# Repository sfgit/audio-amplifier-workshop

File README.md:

# audio-amplifier-workshop
simple audio amplifier workshop files

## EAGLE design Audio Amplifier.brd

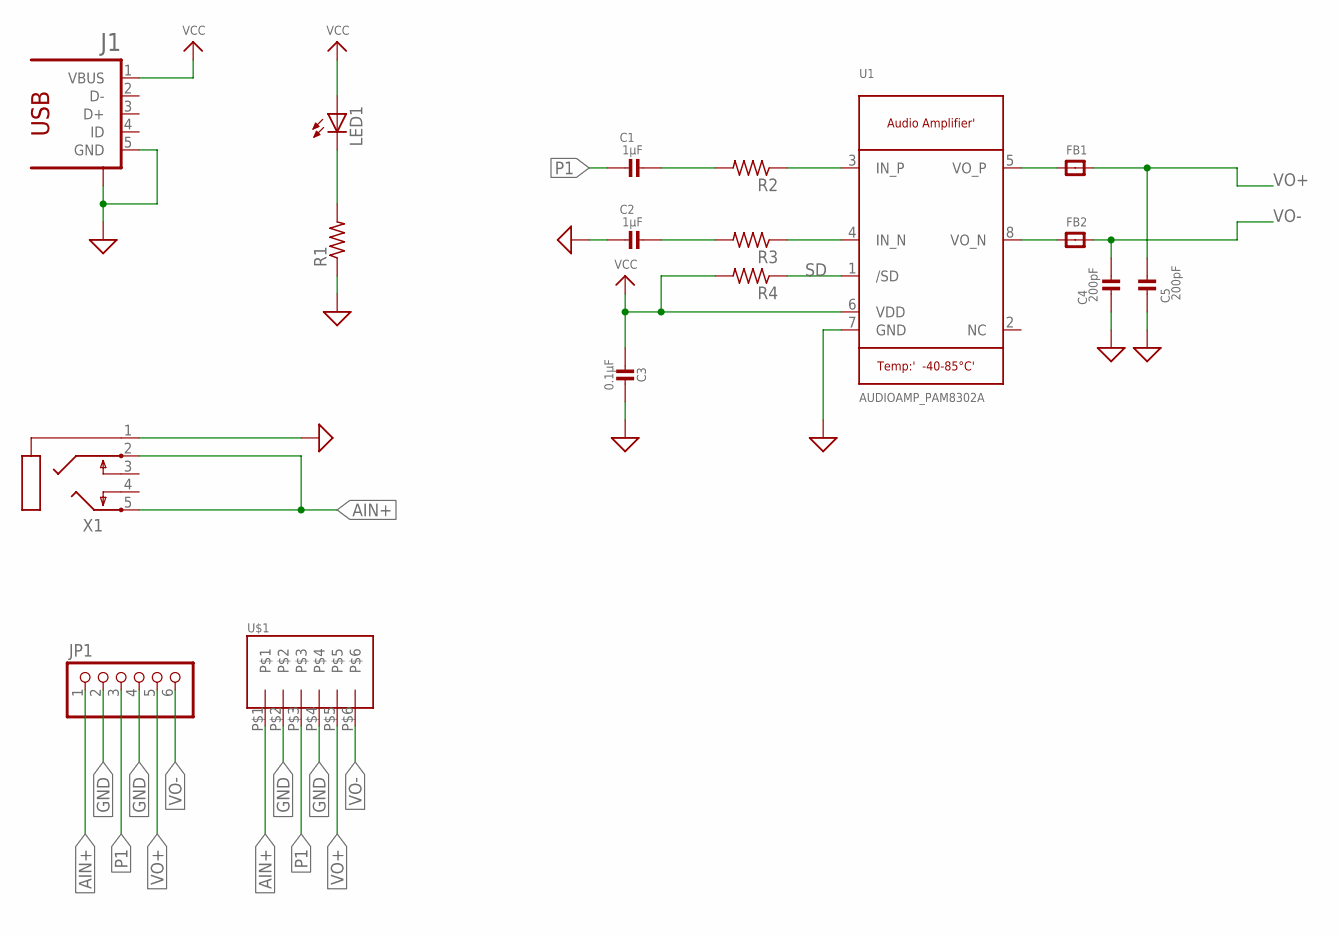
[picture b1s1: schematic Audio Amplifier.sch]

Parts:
C1, C2: 1µF; 0805-NO
C3: 0.1µF; 0805-NO
C4, C5: 200pF; 0805-NO
FB1, FB2: FERRITE_0805; _0805
J1: 1981584-1
JP1: PINHD-1X6; 1X06
LED1: LEDCHIPLED_0603; CHIPLED_0603
R1: 330Ω; R0603
R2, R3: 100Ω; R0603
R4: 10KΩ; R0603
U1: AUDIOAMP_PAM8302A; MSOP8_0.65MM
U$1: 90814-0806
X1: STEREOJACK; STX3100

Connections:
AIN+: JP1.1, U$1.P$1, X1.2, X1.5
GND: C2.1, C3.1, C4.1, C5.1, J1.5 (GND), J1.S1, JP1.2, JP1.4, R1.1, U1.7 (GND), U$1.P$2, U$1.P$4, X1.1
unnamed: R3.1, U1.4 (IN_N)
unnamed: R2.1, U1.3 (IN_P)
unnamed: C1.2, R2.2
unnamed: C2.2, R3.2
unnamed: FB1.1, U1.5 (VO_P)
unnamed: FB2.1, U1.8 (VO_N)
unnamed: LED1.C, R1.2
P1: C1.1, JP1.3, U$1.P$3
SD: R4.1, U1.1 (/SD)
VCC: C3.2, J1.1 (VBUS), LED1.A, R4.2, U1.6 (VDD)
VO+: C5.2, FB1.2, JP1.5, U$1.P$5
VO-: C4.2, FB2.2, JP1.6, U$1.P$6

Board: 2 copper layers, 17 parts (0 on the bottom side), 14 nets, no tracks yet.
